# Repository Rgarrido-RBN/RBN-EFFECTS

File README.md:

# RBN-EFFECTS

## EN/

These are some of the projects I built and I make my own layout. Feel free to extend my work and experiment or modify whith them. 
Some of them are not verified, so before building them please check the schematic and the layout of the project.

**Non for comercial use.**

## ES/

Estos son algunos de los proyectos que he ido desarrollando por mi cuenta. Siéntete libre de fabricarlos y modificarlos. 
Algunos de los diseños no están verificados, si vas a construir alguno directamente asegurate de que el esquematico y las pistas estan corregidas.

**No para un uso comercial.**

Any suggestion or doubt contact me on rgarrido.rbn@gmail.com

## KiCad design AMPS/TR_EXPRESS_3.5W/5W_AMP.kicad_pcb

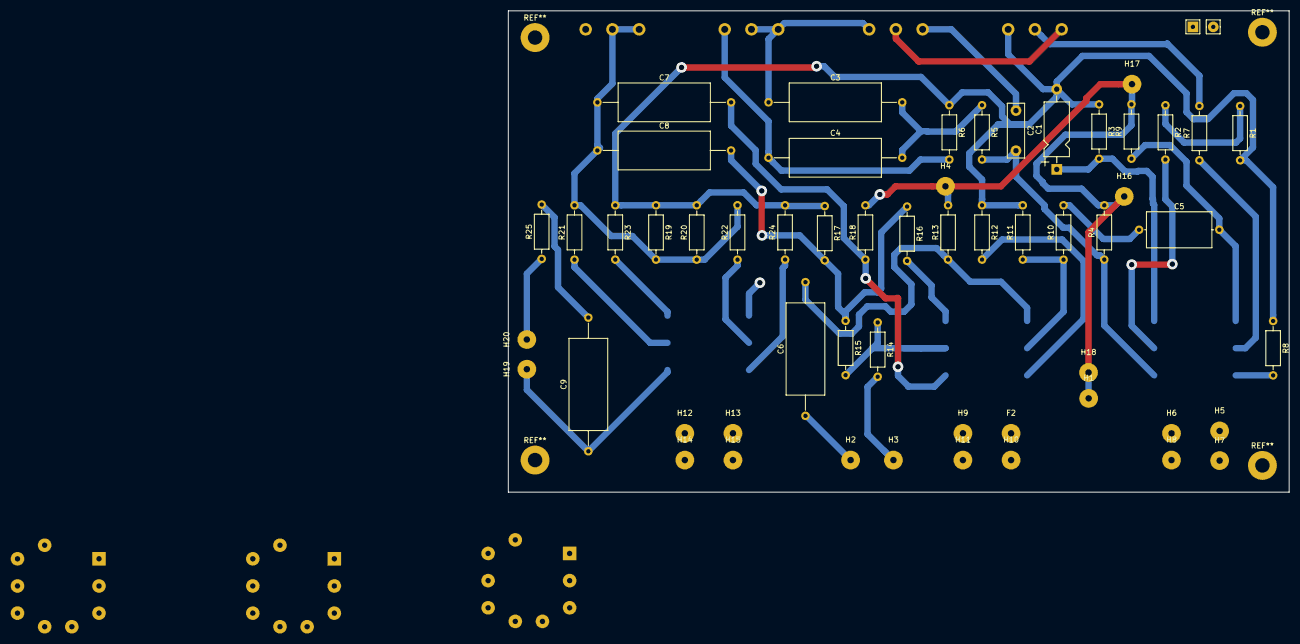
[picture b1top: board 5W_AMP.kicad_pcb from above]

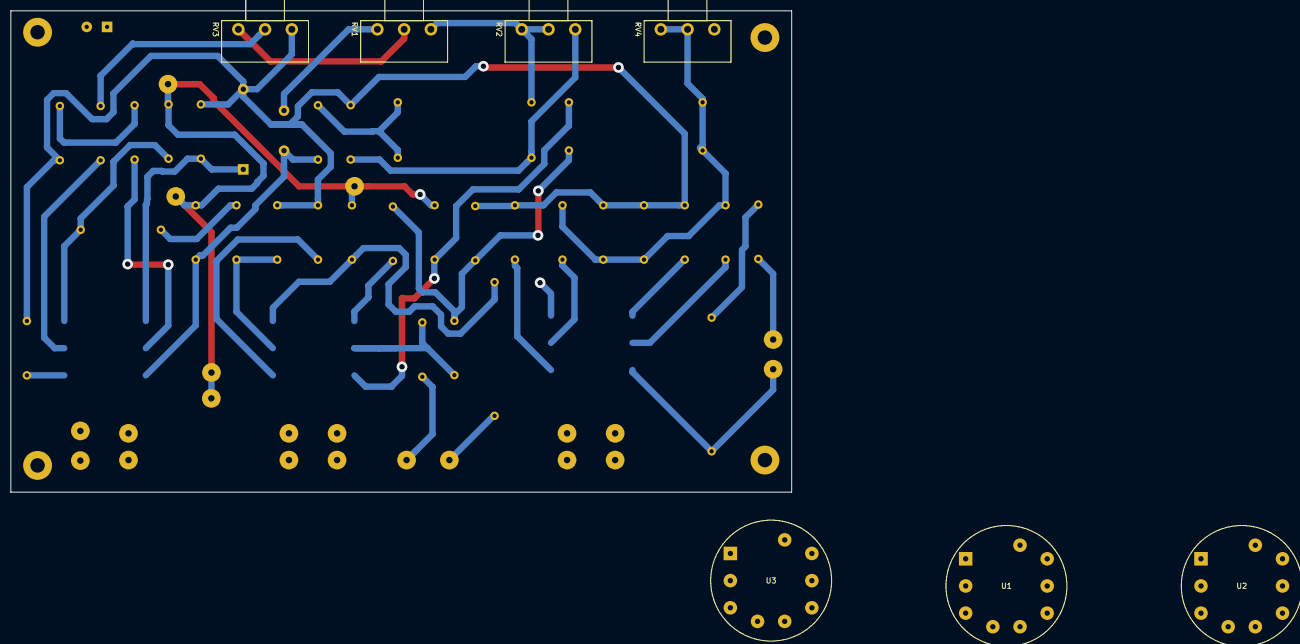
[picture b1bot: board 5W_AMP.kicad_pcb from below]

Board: 2 copper layers, 146.0 x 90.0 mm, 63 parts (7 on the bottom side), 39 nets.

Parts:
C1: 1µ; CP_Axial_L10.0mm_D4.5mm_P15.00mm_Horizontal
C2: 500p; C_Rect_L10.0mm_W3.0mm_P7.50mm_FKS3_FKP3
C3, C4, C6, C7, C8, C9: 22n; C_Axial_L17.0mm_D7.0mm_P25.00mm_Horizontal
C5: 4n7; C_Axial_L12.0mm_D6.5mm_P15.00mm_Horizontal
F2: F2; SolderWirePad_1x01_Drill1.2mm
H1, H4, H16, H17, H18: B1+; SolderWirePad_1x01_Drill1.2mm
H2: SEND; SolderWirePad_1x01_Drill1.2mm
H3: RETURN; SolderWirePad_1x01_Drill1.2mm
H5, H6, H9, H12, H13, H19, H20: F2; SolderWirePad_1x01_Drill1.2mm
H7, H8, H10, H11, H14, H15: F1; SolderWirePad_1x01_Drill1.2mm
J1: AudioJack2; Audio_Jack_Mono
R1, R14: 1M; R_Axial_DIN0207_L6.3mm_D2.5mm_P10.16mm_Horizontal
R2: 68k; R_Axial_DIN0207_L6.3mm_D2.5mm_P10.16mm_Horizontal
R3, R12, R16: 1k5; R_Axial_DIN0207_L6.3mm_D2.5mm_P10.16mm_Horizontal
R4, R9, R13: 100k; R_Axial_DIN0207_L6.3mm_D2.5mm_P10.16mm_Horizontal
R5: 150k; R_Axial_DIN0207_L6.3mm_D2.5mm_P10.16mm_Horizontal
R6: 15k; R_Axial_DIN0207_L6.3mm_D2.5mm_P10.16mm_Horizontal
R7: 820R; R_Axial_DIN0207_L6.3mm_D2.5mm_P10.16mm_Horizontal
R8: 2k7; R_Axial_DIN0207_L6.3mm_D2.5mm_P10.16mm_Horizontal
R10, R11: 470k; R_Axial_DIN0207_L6.3mm_D2.5mm_P10.16mm_Horizontal
R15, R19, R20: 220k; R_Axial_DIN0207_L6.3mm_D2.5mm_P10.16mm_Horizontal
R17, R18: 47k; R_Axial_DIN0207_L6.3mm_D2.5mm_P10.16mm_Horizontal
R21, R22: 22k; R_Axial_DIN0207_L6.3mm_D2.5mm_P10.16mm_Horizontal
R23, R24: 560R; R_Axial_DIN0207_L6.3mm_D2.5mm_P10.16mm_Horizontal
R25: 10k; R_Axial_DIN0207_L6.3mm_D2.5mm_P10.16mm_Horizontal
RV1, RV4: A250k; Potentiometer_Piher_T-16H_Single_Horizontal
RV2, RV3: A1M; Potentiometer_Piher_T-16H_Single_Horizontal
U1, U2: ECC83; Valve_Noval_P
U3: ECC99; Valve_Noval_P

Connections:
B1: H1.1, H4.1, H16.1, H17.1, H18.1, R4.2, R9.2, R13.2, R18.2
GND: C1.2, R1.2, R3.1, R6.1, R8.1, R11.2, R12.1, R17.1, R19.1, R20.2, R23.1, R24.2, RV3.1
unnamed: C1.1, R3.2, U1.8
unnamed: C2.1, RV1.3
unnamed: C2.2, R4.1, R5.2, U1.6
unnamed: C3.1, RV1.1, RV2.2, RV2.3
unnamed: C3.2, C4.2, R5.1
unnamed: C4.1, R6.2, RV2.1
unnamed: C5.1, R10.2
unnamed: C5.2, R9.1, U1.1
unnamed: C6.1, H2.1
unnamed: C6.2, R13.1, U2.1
unnamed: C7.1, C8.1, R19.2, R20.1, R21.2, R22.2, RV4.2, RV4.3
unnamed: C7.2, R18.1, U2.6
unnamed: C8.2, R15.1, R16.1, R17.2
unnamed: C9.1, H19.1, U3.6
unnamed: C9.2, R25.2
unnamed: F2.1, H9.1, U2.9
unnamed: H3.1, R14.2
unnamed: H5.1, H6.1, U1.9
unnamed: H7.1, H8.1, U1.4, U1.5
unnamed: H10.1, H11.1, U2.4, U2.5
unnamed: H12.1, H13.1, U3.9
unnamed: H14.1, H15.1, U3.4, U3.5
unnamed: H20.1, R25.1, U3.1
unnamed: R1.1, R2.1
unnamed: R2.2, U1.7
unnamed: R7.1, U1.2
unnamed: R7.2, RV3.2
unnamed: R8.2, U1.3
unnamed: R10.1, R11.1, U2.2
unnamed: R12.2, U2.3
unnamed: R14.1, R15.2, U2.7
unnamed: R16.2, U2.8
unnamed: R21.1, U3.7
unnamed: R22.1, U3.2
unnamed: R23.2, U3.8
unnamed: R24.1, U3.3
unnamed: RV1.2, RV3.3

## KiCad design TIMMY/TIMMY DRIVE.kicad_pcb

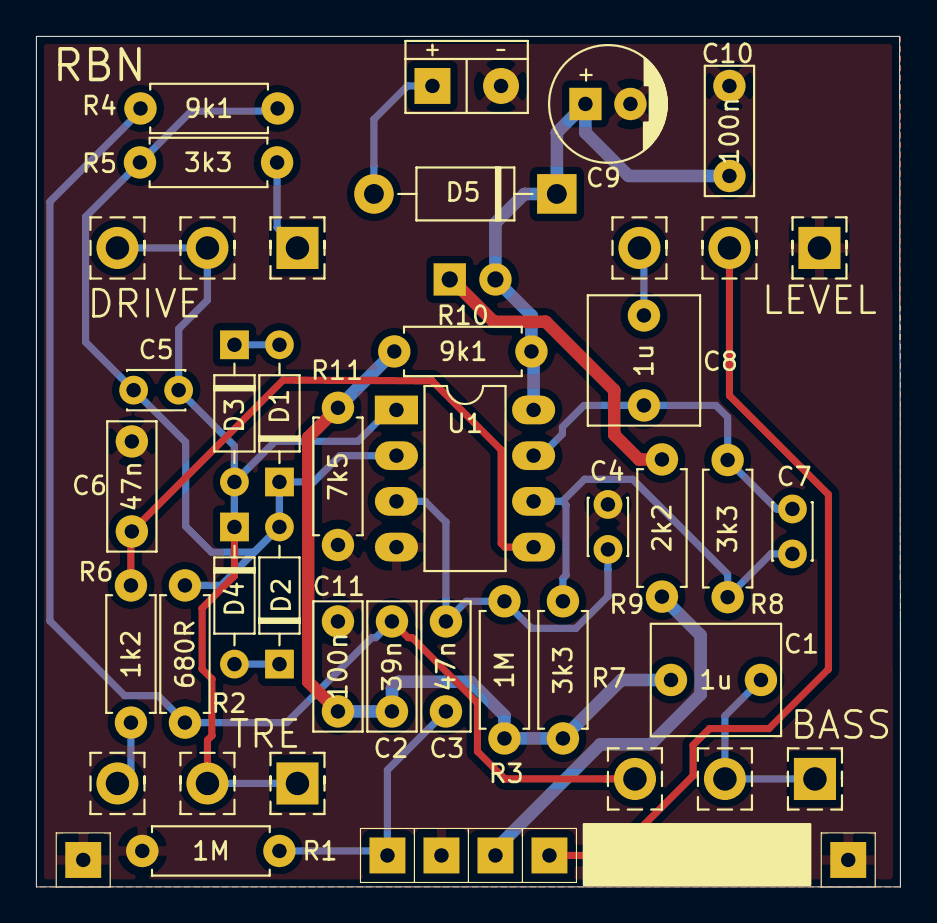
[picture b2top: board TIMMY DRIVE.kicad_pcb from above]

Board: 2 copper layers, 48.0 x 47.2 mm, 40 parts (1 on the bottom side), 21 nets.

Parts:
BT1: Battery_Cell; PWR_CON
C1, C8: 1u; Cap_poly_big
C2: 39n; Cap_poly_little
C3, C6: 47n; Cap_poly_little
C4: 22p; C_Disc_D3.0mm_W2.0mm_P2.50mm
C5: 47p; C_Disc_D3.0mm_W2.0mm_P2.50mm
C7: 150p; C_Disc_D3.0mm_W2.0mm_P2.50mm
C9: 47u; CP_Radial_D6.3mm_P2.50mm
C10, C11: 100n; Cap_poly_little
D1, D2, D3, D4: Si; D_DO-35_SOD27_P7.62mm_Horizontal
D5: D; D_DO-41_SOD81_P10.16mm_Horizontal
D6: LED; LED_D5.0mm
H3, H4, H5: GND; SolderWirePad_1x01_Drill0.8mm
H12: SW; SolderWirePad_1x01_Drill0.8mm
H14: FX.IN; SolderWirePad_1x01_Drill0.8mm
H16: FX.OUT; SolderWirePad_1x01_Drill0.8mm
R1, R3: 1M; R_0.25W_HZ
R2: 680R; R_0.25W_HZ
R4, R10: 9k1; R_0.25W_HZ
R5, R7, R8: 3k3; R_0.25W_HZ
R6: 1k2; R_0.25W_HZ
R9: 2k2; R_0.25W_HZ
R11: 7k5; R_0.25W_HZ
RV1: B50k; Pot_16_Alpha
RV3: B500k; Pot_16_Alpha
RV4, RV5: B10k; Pot_16_Alpha
U1: TL072; DIP-8_W7.62mm_LongPads

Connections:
FX.IN: C3.1, H14.1, R1.1
FX.OUT: H16.1, RV5.2
GND: BT1.2, C4.1, C6.1, C9.2, C10.1, C11.1, H3.1, H4.1, H5.1, R1.2, R11.1, RV5.1, U1.4
unnamed: BT1.1, D5.2
unnamed: C1.2, RV1.1, RV1.2
unnamed: C2.2, R2.1, R4.1, RV1.3
unnamed: C3.2, C4.2, R3.1, U1.3
unnamed: C5.1, D1.1, D2.2, R2.2, R4.2, R5.1, U1.2
unnamed: C5.2, D3.2, D4.1, RV3.2, RV3.3, RV4.1, RV4.2, U1.1
unnamed: C6.2, R6.2, U1.5
unnamed: C7.1, C8.2, R8.2, U1.7
unnamed: C7.2, R7.2, R8.1, U1.6
unnamed: C8.1, RV5.3
unnamed: C9.1, C10.2, D5.1, D6.2, R10.1, U1.8
unnamed: D1.2, D3.1
unnamed: D2.1, D4.2
unnamed: D6.1, R9.1
unnamed: R5.2, RV3.1
unnamed: R6.1, RV4.3
SW: H12.1, R9.2
Vref: C1.1, C2.1, C11.2, R3.2, R7.1, R10.2, R11.2

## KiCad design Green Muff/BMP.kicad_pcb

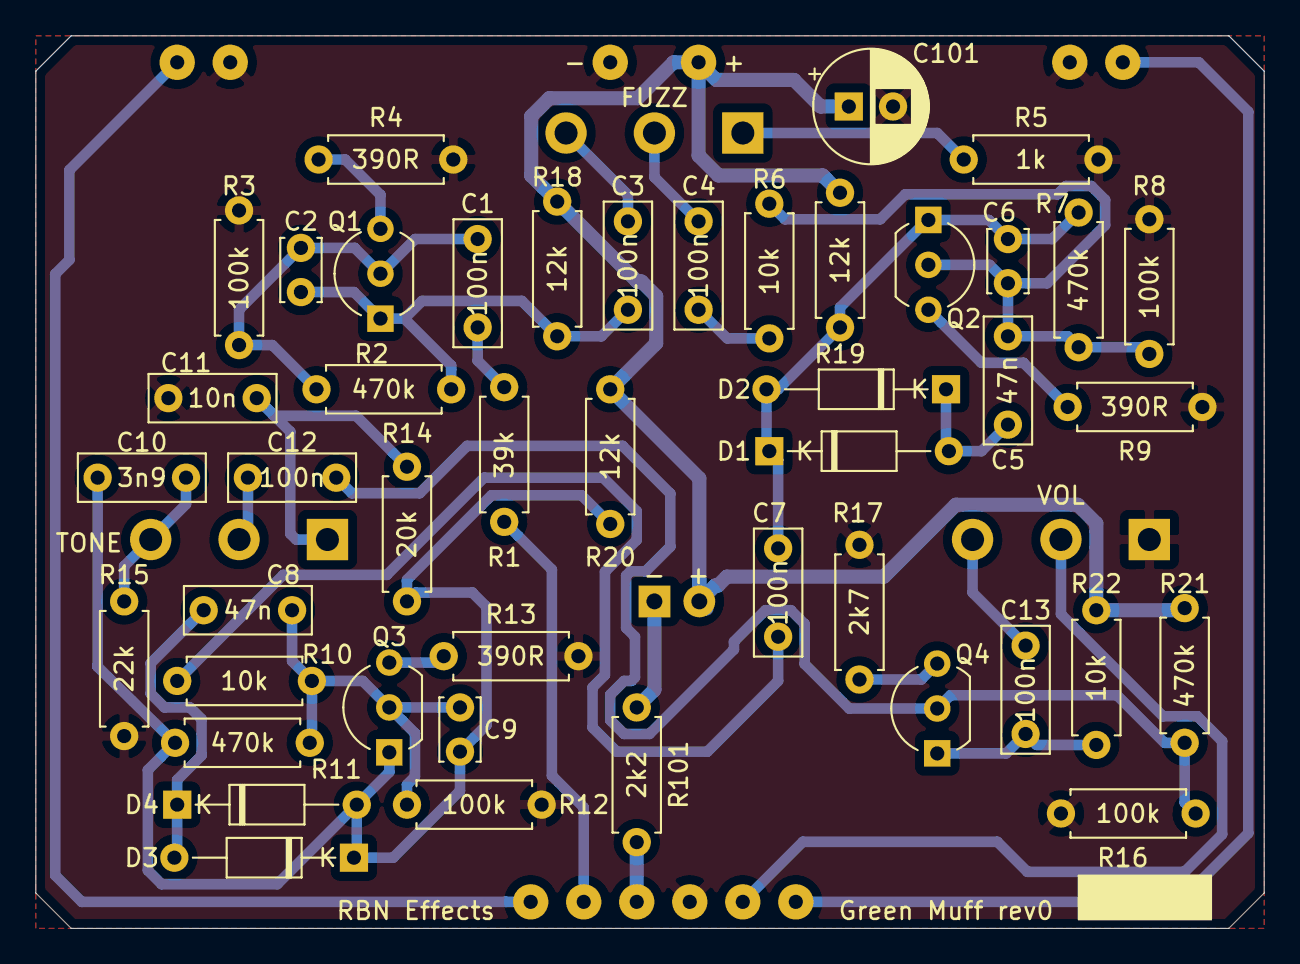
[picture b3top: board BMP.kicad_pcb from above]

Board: 2 copper layers, 69.5 x 50.5 mm, 61 parts (1 on the bottom side), 32 nets.

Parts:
C1, C3, C4, C7, C12, C13: 100n; Cap_POLY_SMALL
C2, C6, C9: 470p; C_Disc_D3.4mm_W2.1mm_P2.50mm
C5, C8: 47n; Cap_POLY_SMALL
C10: 3n9; Cap_POLY_SMALL
C11: 10n; Cap_POLY_SMALL
C101: 22u; CP_Radial_D6.3mm_P2.50mm
D1, D2, D3, D4: 1N914; D_DO-35_SOD27_P10.16mm_Horizontal
D5: LED; LED_D5.0mm
H2, H3: IN; SolderWirePad_1x01_Drill0.8mm
H4, H9: OUT; SolderWirePad_1x01_Drill0.8mm
H5: 9V; SolderWirePad_1x01_Drill0.8mm
H6, H7, H8, H10: GND; SolderWirePad_1x01_Drill0.8mm
H11: OUT FX; SolderWirePad_1x01_Drill0.8mm
H14: SW; SolderWirePad_1x01_Drill0.8mm
H15: IN FX; SolderWirePad_1x01_Drill0.8mm
Q1, Q2, Q3, Q4: BC549C; TO-92_Inline_Wide
R1: 39k; R_0.25W_HZ
R2, R7, R11, R21: 470k; R_0.25W_HZ
R3, R8, R12, R16: 100k; R_0.25W_HZ
R4, R9, R13: 390R; R_0.25W_HZ
R5: 1k; R_0.25W_HZ
R6, R10, R22: 10k; R_0.25W_HZ
R14: 20k; R_0.25W_HZ
R15: 22k; R_0.25W_HZ
R17: 2k7; R_0.25W_HZ
R18, R19, R20: 12k; R_0.25W_HZ
R101: 2k2; R_0.25W_HZ
RV1, RV2, RV3: B100k; Potentiometer_Piher_T-16L_Single_Vertical_Hole_MOD

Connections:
GND: C11.1, C101.2, H6.1, H7.1, H8.1, H10.1, R3.2, R4.2, R5.2, R8.2, R9.2, R12.2, R13.2, R15.2, R16.1, R17.1, RV3.1
IN: H2.1, H3.1
IN_FX: H15.1, R1.1
unnamed: C1.1, R1.2
unnamed: C1.2, C2.1, Q1.2, R2.1, R3.1
unnamed: C2.2, C3.1, Q1.1, R2.2, R18.2
unnamed: C3.2, RV1.3
unnamed: C4.1, RV1.2
unnamed: C4.2, R6.1
unnamed: C5.1, C6.1, Q2.2, R6.2, R7.1, R8.1
unnamed: C5.2, D1.2, D2.1
unnamed: C6.2, C7.1, D1.1, D2.2, Q2.1, R7.2, R19.2
unnamed: C7.2, R10.1
unnamed: C8.1, C9.1, Q3.2, R10.2, R11.1, R12.1
unnamed: C8.2, D3.2, D4.1
unnamed: C9.2, C10.1, D3.1, D4.2, Q3.1, R11.2, R14.1, R20.2
unnamed: C10.2, R15.1, RV2.3
unnamed: C11.2, R14.2, RV2.1
unnamed: C12.1, Q4.2, R16.2, R21.1
unnamed: C12.2, RV2.2
unnamed: C13.1, RV3.3
unnamed: C13.2, Q4.1, R22.1
unnamed: D5.1, R101.1
unnamed: Q1.3, R4.1
unnamed: Q2.3, R9.1
unnamed: Q3.3, R13.1
unnamed: Q4.3, R17.2
unnamed: R5.1, RV1.1
OUT: H4.1, H9.1
OUT_FX: H11.1, RV3.2
SW: H14.1, R101.2
V+: C101.1, D5.2, H5.1, R18.1, R19.1, R20.1, R21.2, R22.2

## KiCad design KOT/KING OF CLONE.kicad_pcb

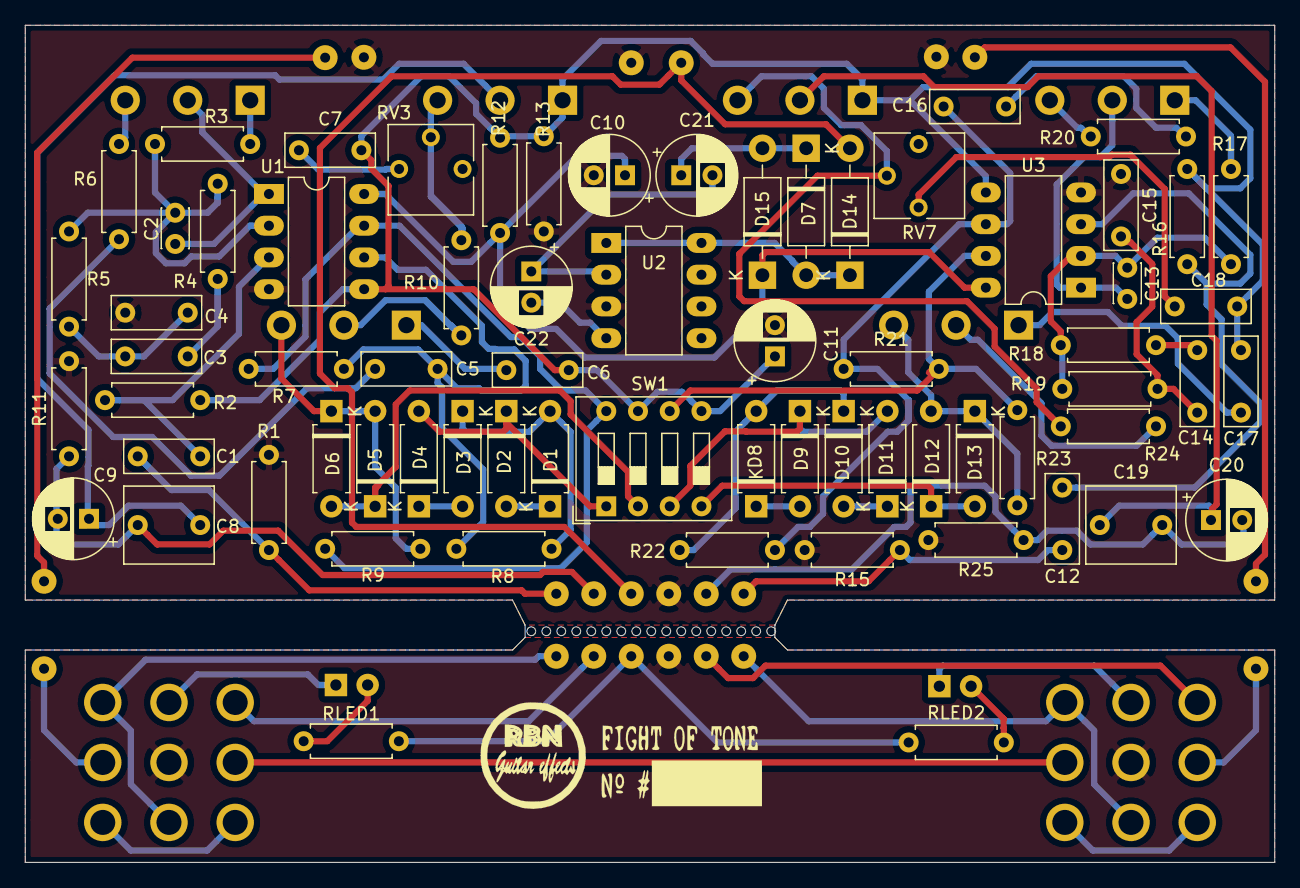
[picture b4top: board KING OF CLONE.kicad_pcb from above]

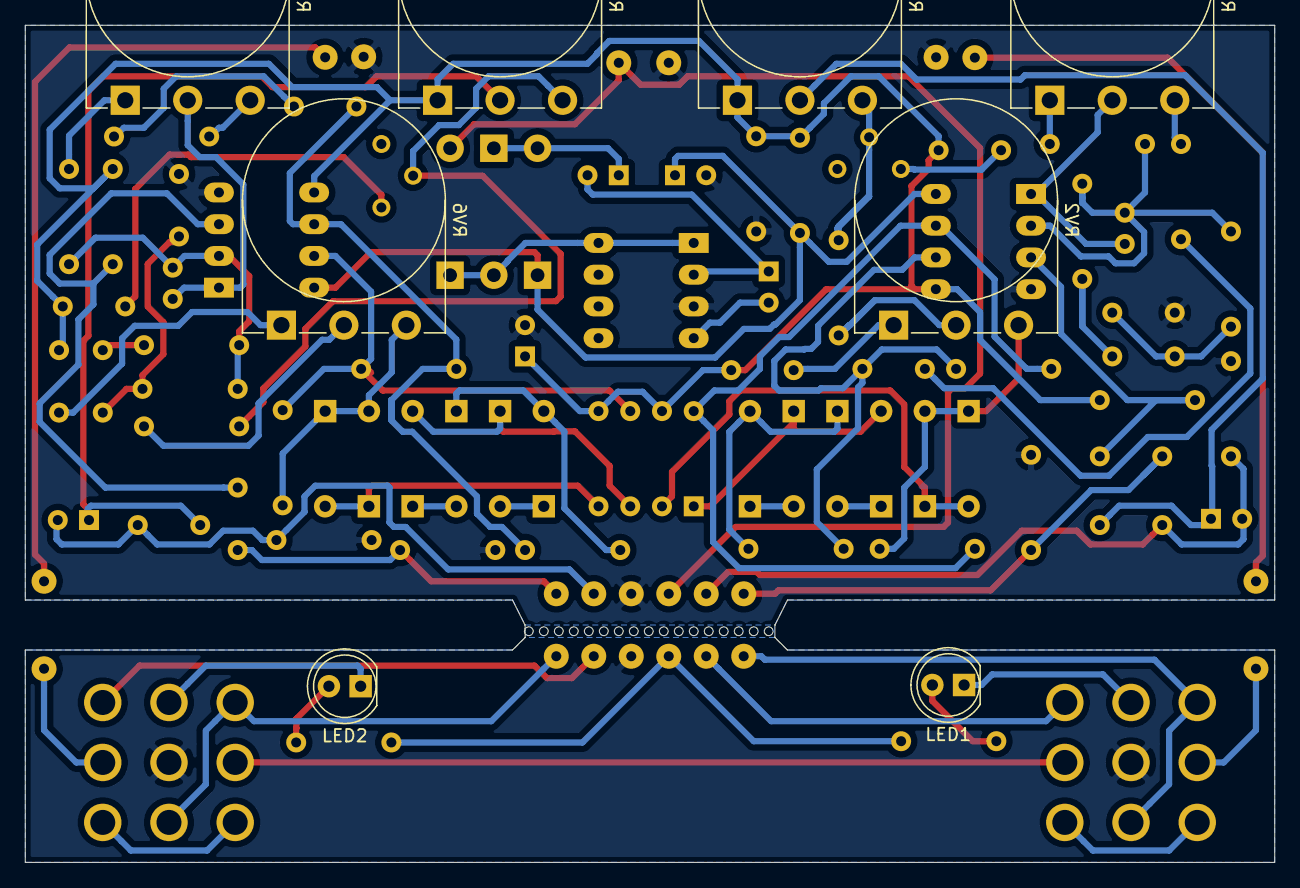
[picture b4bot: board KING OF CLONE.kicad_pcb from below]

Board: 2 copper layers, 100.0 x 67.0 mm, 101 parts (2 on the bottom side), 63 nets.

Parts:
C1, C3, C4, C6, C7, C12, C14, C15, C17, C18: 10n; C_Rect_L7.0mm_W2.5mm_P5.00mm
C2, C13: 100p; C_Disc_D3.0mm_W2.0mm_P2.50mm
C5, C16: 100n; C_Rect_L7.0mm_W2.5mm_P5.00mm
C8, C19: 1u; C_Rect_L7.0mm_W6.0mm_P5.00mm
C9, C20: 1u; CP_Radial_D6.3mm_P2.50mm
C10, C21, C22: 10u; CP_Radial_D6.3mm_P2.50mm
C11: 100u; CP_Radial_D6.3mm_P2.50mm
D1, D2, D3, D4, D8, D9, D10, D11: MA856; D_A-405_P7.62mm_Horizontal
D5, D6, D12, D13: 1S1588; D_A-405_P7.62mm_Horizontal
D7, D14, D15: 5817; D_DO-41_SOD81_P10.16mm_Horizontal
H1, H7, H9, H13, H15, H101, H103: IN; SolderWirePad_1x01_Drill0.8mm
H2, H8, H10, H14, H16, H102, H104: OUT; SolderWirePad_1x01_Drill0.8mm
H3, H11, H17: 9V; SolderWirePad_1x01_Drill0.8mm
H4, H5, H6, H12, H18: GND; SolderWirePad_1x01_Drill0.8mm
LED1, LED2: LED; LED_D5.0mm
R1, R2, R11, R15, R16, R25: 1M; R_Axial_DIN0207_L6.3mm_D2.5mm_P7.62mm_Horizontal
R3, R6, R17, R20: 10k; R_Axial_DIN0207_L6.3mm_D2.5mm_P7.62mm_Horizontal
R4, R18: 33k; R_Axial_DIN0207_L6.3mm_D2.5mm_P7.62mm_Horizontal
R5, R19: 27k; R_Axial_DIN0207_L6.3mm_D2.5mm_P7.62mm_Horizontal
R7, R21: 220k; R_Axial_DIN0207_L6.3mm_D2.5mm_P7.62mm_Horizontal
R8, R10, R22, R24: 6k8; R_Axial_DIN0207_L6.3mm_D2.5mm_P7.62mm_Horizontal
R9, R23: 1k; R_Axial_DIN0207_L6.3mm_D2.5mm_P7.62mm_Horizontal
R12, R13: 47k; R_Axial_DIN0207_L6.3mm_D2.5mm_P7.62mm_Horizontal
RLED1, RLED2: 2k2; R_Axial_DIN0207_L6.3mm_D2.5mm_P7.62mm_Horizontal
RV1, RV5: B100K; Potentiometer_Piher_T-16L_Single_Vertical_Hole_MOD
RV2, RV6: B25K; Potentiometer_Piher_T-16L_Single_Vertical_Hole_MOD
RV3, RV7: B50K; Potentiometer_Vishay_T73YP_Vertical
RV4, RV8: A100K; Potentiometer_Piher_T-16L_Single_Vertical_Hole_MOD
SW1: SW_DIP_4_2cases; SW_DIP_SPSTx04_Slide_9.78x12.34mm_W7.62mm_P2.54mm
SW2, SW3: 3pdt; 3PDT
U1, U3: RC4580; DIP-8_W7.62mm_LongPads
U2: MAX1044; DIP-8_W7.62mm_LongPads

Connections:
+9V: D7.2, H3.1, H11.1, H17.1, RLED1.1, RLED2.1
/POWER_SUPPLY/18V: C21.1, D14.1, D15.2
/POWER_SUPPLY/VCC: C10.1, D15.1, R12.1, U1.8, U3.8
COMMON: SW2.6, SW3.4
GND: C4.2, C10.2, C11.2, C15.2, H4.1, H5.1, H6.1, H12.1, H18.1, R1.2, R11.2, R13.2, R15.2, R25.2, SW2.5, SW3.5, U1.4, U2.3, U3.4
IN1: C1.2, H7.1, H13.1, R1.1, SW2.2, SW2.7
IN2: C12.2, H9.1, H15.1, R15.1, SW3.2, SW3.7
JACK_IN: H1.1, H101.1, H103.1, SW2.4
JACK_OUT: H2.1, H102.1, H104.1, SW3.6
unnamed: C1.1, R2.2, U1.3
unnamed: C2.1, RV1.2, U1.1
unnamed: C2.2, R3.2, R4.2, R5.1, U1.2
unnamed: C3.1, R4.1
unnamed: C3.2, C4.1, R5.2
unnamed: C5.1, R7.1, R8.1, U1.6
unnamed: C5.2, R6.2
unnamed: C6.1, RV2.1
unnamed: C7.1, RV3.3
unnamed: C8.1, C9.1, RV4.2
unnamed: C12.1, R16.2, U3.3
unnamed: C13.1, RV5.2, U3.1
unnamed: C13.2, R17.2, R18.2, R19.1, U3.2
unnamed: C14.1, R18.1
unnamed: C14.2, C15.1, R19.2
unnamed: C16.1, R21.1, R22.1, U3.6
unnamed: C16.2, R20.2
unnamed: C17.1, RV6.1
unnamed: C18.1, RV7.3
unnamed: C19.1, C20.1, RV8.2
unnamed: C21.2, C22.1, U2.2
unnamed: C22.2, U2.4
unnamed: D1.1, D2.2
unnamed: D1.2, D3.1, R8.2
unnamed: D2.1, D4.2, SW1.1
unnamed: D3.2, D4.1
unnamed: D5.1, D6.2, SW1.2
unnamed: D5.2, D6.1, R9.2, RV2.3
unnamed: D8.1, D9.2
unnamed: D8.2, D10.1, R22.2
unnamed: D10.2, D11.1
unnamed: D9.1, D11.2, SW1.3
unnamed: D12.1, D13.2, SW1.4
unnamed: D12.2, D13.1, R23.2, RV6.3
unnamed: D7.1, D14.2, U2.1, U2.8
unnamed: LED1.2, RLED1.2
unnamed: LED2.2, RLED2.2
unnamed: R3.1, RV1.1
unnamed: R6.1, RV1.3
unnamed: R7.2, R9.1, SW1.8, U1.7
unnamed: R10.1, RV2.2
unnamed: R10.2, RV3.2, RV4.3
unnamed: R17.1, RV5.1
unnamed: R20.1, RV5.3
unnamed: R21.2, R23.1, SW1.6, U3.7
unnamed: R24.1, RV6.2
unnamed: R24.2, RV7.2, RV8.3
unnamed: SW2.1, SW2.3
unnamed: SW3.1, SW3.3
OUT1: C8.2, C9.2, H8.1, H14.1, R11.1, SW2.9
OUT2: C19.2, C20.2, H10.1, H16.1, R25.1, SW3.9
SW1: LED1.1, SW2.8
SW2: LED2.1, SW3.8
VREF: C6.2, C7.2, C11.1, C17.2, C18.2, R2.1, R12.2, R13.1, R16.1, RV4.1, RV8.1, SW1.5, SW1.7, U1.5, U3.5

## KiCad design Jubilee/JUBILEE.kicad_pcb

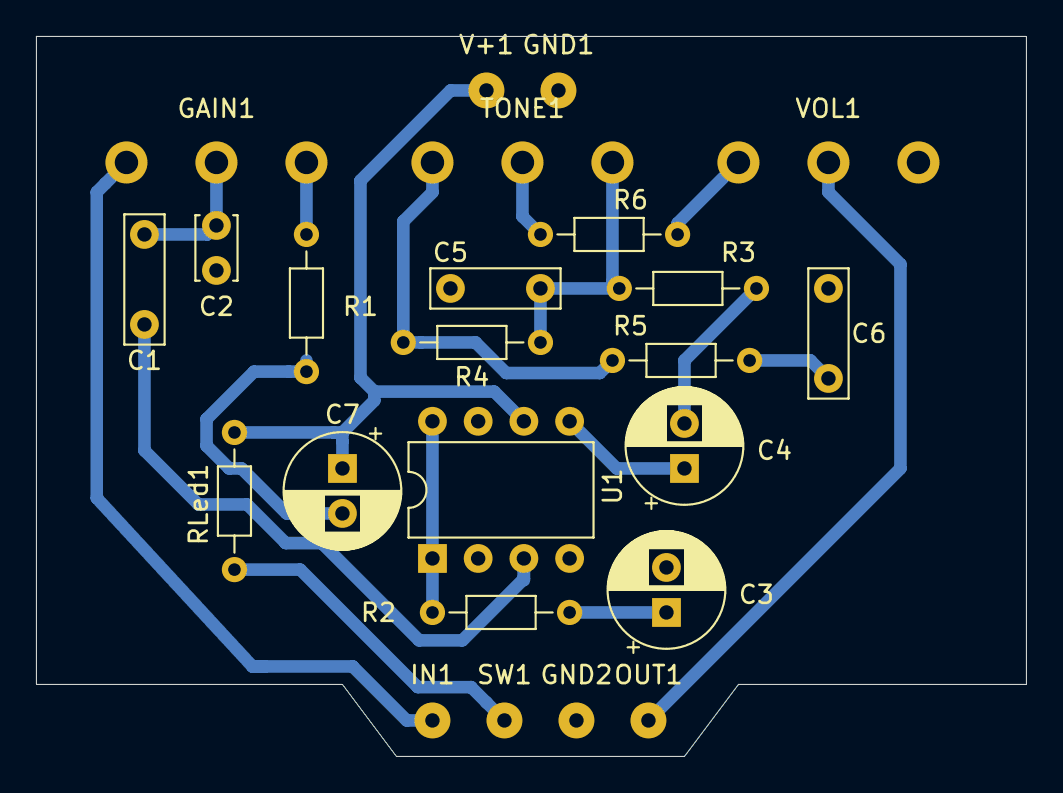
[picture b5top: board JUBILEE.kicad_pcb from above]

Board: 2 copper layers, 55.0 x 40.0 mm, 24 parts (0 on the bottom side), 17 nets.

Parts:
C1: 390p; C_Disc_D3.4mm_W2.1mm_P2.50mm
C2, C5: 22n; C_Rect_L7.0mm_W2.0mm_P5.00mm
C3, C4, C7: 47u; CP_Radial_D6.3mm_P2.50mm
C6: 100n; C_Rect_L7.0mm_W2.0mm_P5.00mm
GAIN1: A250k; Potentiometer_Piher_T-16L_Single_Vertical_Hole_MOD
GND1, GND2: MountingHole_Pad; SolderWirePad_1x01_Drill0.8mm
IN1: MountingHole_Pad; SolderWirePad_1x01_Drill0.8mm
OUT1: MountingHole_Pad; SolderWirePad_1x01_Drill0.8mm
R1, R3, R4: 4k7; R_Axial_DIN0204_L3.6mm_D1.6mm_P7.62mm_Horizontal
R2: 47R; R_Axial_DIN0204_L3.6mm_D1.6mm_P7.62mm_Horizontal
R5: 1k8; R_Axial_DIN0204_L3.6mm_D1.6mm_P7.62mm_Horizontal
R6: 330R; R_Axial_DIN0204_L3.6mm_D1.6mm_P7.62mm_Horizontal
RLed1: R; R_Axial_DIN0204_L3.6mm_D1.6mm_P7.62mm_Horizontal
SW1: MountingHole_Pad; SolderWirePad_1x01_Drill0.8mm
TONE1: B50k; Potentiometer_Piher_T-16L_Single_Vertical_Hole_MOD
U1: LM386; DIP-8_W7.62mm
V+1: MountingHole_Pad; SolderWirePad_1x01_Drill0.8mm
VOL1: A100k; Potentiometer_Piher_T-16L_Single_Vertical_Hole_MOD

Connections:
GND: C1.1, C3.2, C5.1, C6.1, C7.2, GND1.1, GND2.1, R1.2, U1.2, U1.4, VOL1.1
unnamed: C1.2, C2.1, GAIN1.2
unnamed: C2.2, U1.3
unnamed: C3.1, R2.2
unnamed: C4.1, U1.5
unnamed: C4.2, R3.1
unnamed: C5.2, R3.2, R4.1, TONE1.3
unnamed: C6.2, R5.2
unnamed: C7.1, RLed1.1, U1.6, V+1.1
unnamed: GAIN1.1, R1.1
unnamed: GAIN1.3, IN1.1
unnamed: OUT1.1, VOL1.2
unnamed: R2.1, U1.1, U1.8
unnamed: R4.2, R5.1, TONE1.1
unnamed: R6.1, TONE1.2
unnamed: R6.2, VOL1.3
unnamed: RLed1.2, SW1.1

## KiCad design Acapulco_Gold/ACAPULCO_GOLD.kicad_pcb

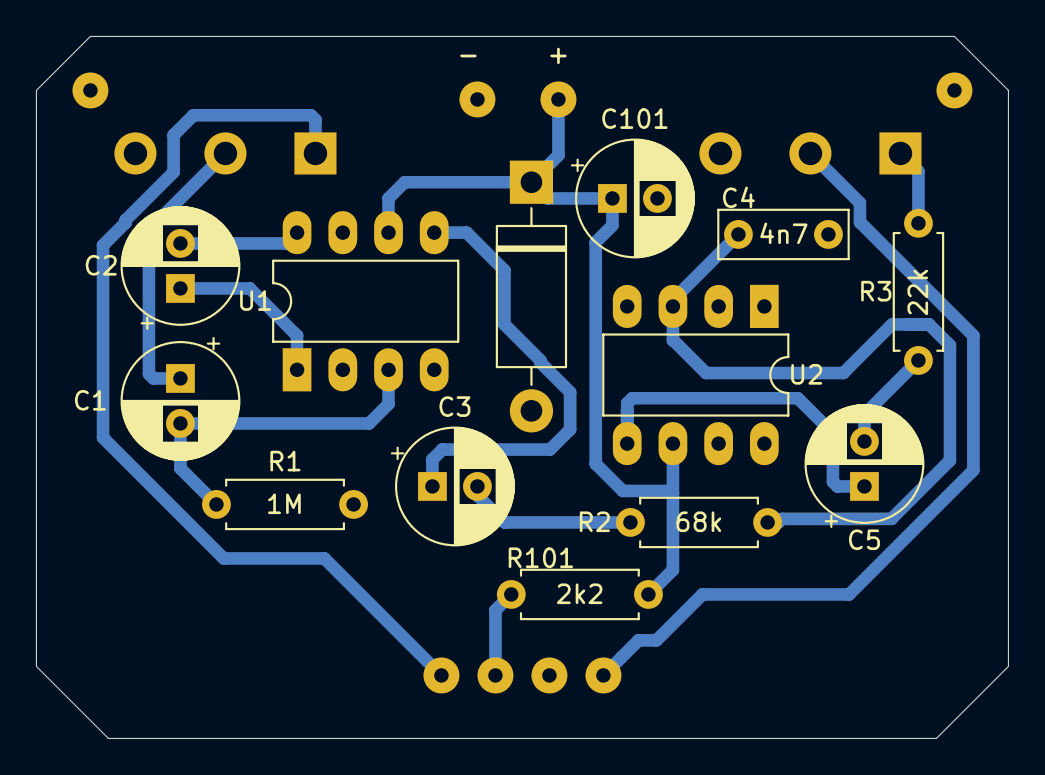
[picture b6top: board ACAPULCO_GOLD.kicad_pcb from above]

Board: 2 copper layers, 54.0 x 39.0 mm, 23 parts (0 on the bottom side), 15 nets.

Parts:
C1, C2: 10u; CP_Radial_D6.3mm_P2.50mm
C3, C5: 1u; CP_Radial_D6.3mm_P2.50mm
C4: 4n7; Cap_POLY_SMALL
C101: 47u; CP_Radial_D6.3mm_P2.50mm
D101: 1N4001; D_DO-15_P12.70mm_Horizontal
H5: PCB_OUT; SolderWirePad_1x01_Drill0.8mm
H6: PCB_IN; SolderWirePad_1x01_Drill0.8mm
H7, H8, H9, H10: GND; SolderWirePad_1x01_Drill0.8mm
H11: 9V; SolderWirePad_1x01_Drill0.8mm
H12: SW; SolderWirePad_1x01_Drill0.8mm
R1: 1M; R_0.25W_HZ
R2: 68k; R_0.25W_HZ
R3: 22k; R_0.25W_HZ
R101: 2k2; R_0.25W_HZ
RV1: A500k; Potentiometer_Piher_T-16L_Single_Vertical_Hole_MOD
RV2: A100k; Potentiometer_Piher_T-16L_Single_Vertical_Hole_MOD
U1, U2: LM386; DIP-8_W7.62mm_LongPads

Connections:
+9V: C101.1, D101.1, H11.1, R101.1, U1.6, U2.6
GND: C4.2, C101.2, D101.2, H7.1, H8.1, H9.1, H10.1, R1.2, RV1.3, RV2.3, U1.2, U1.4, U2.2, U2.4
unnamed: C1.1, RV1.2
unnamed: C1.2, R1.1, U1.3
unnamed: C2.1, U1.1
unnamed: C2.2, U1.8
unnamed: C3.1, U1.5
unnamed: C3.2, R2.1
unnamed: C4.1, R2.2, U2.3
unnamed: C5.1, U2.5
unnamed: C5.2, R3.1
unnamed: R3.2, RV2.1
PCB_IN: H6.1, RV1.1
PCB_OUT: H5.1, RV2.2
SW: H12.1, R101.2

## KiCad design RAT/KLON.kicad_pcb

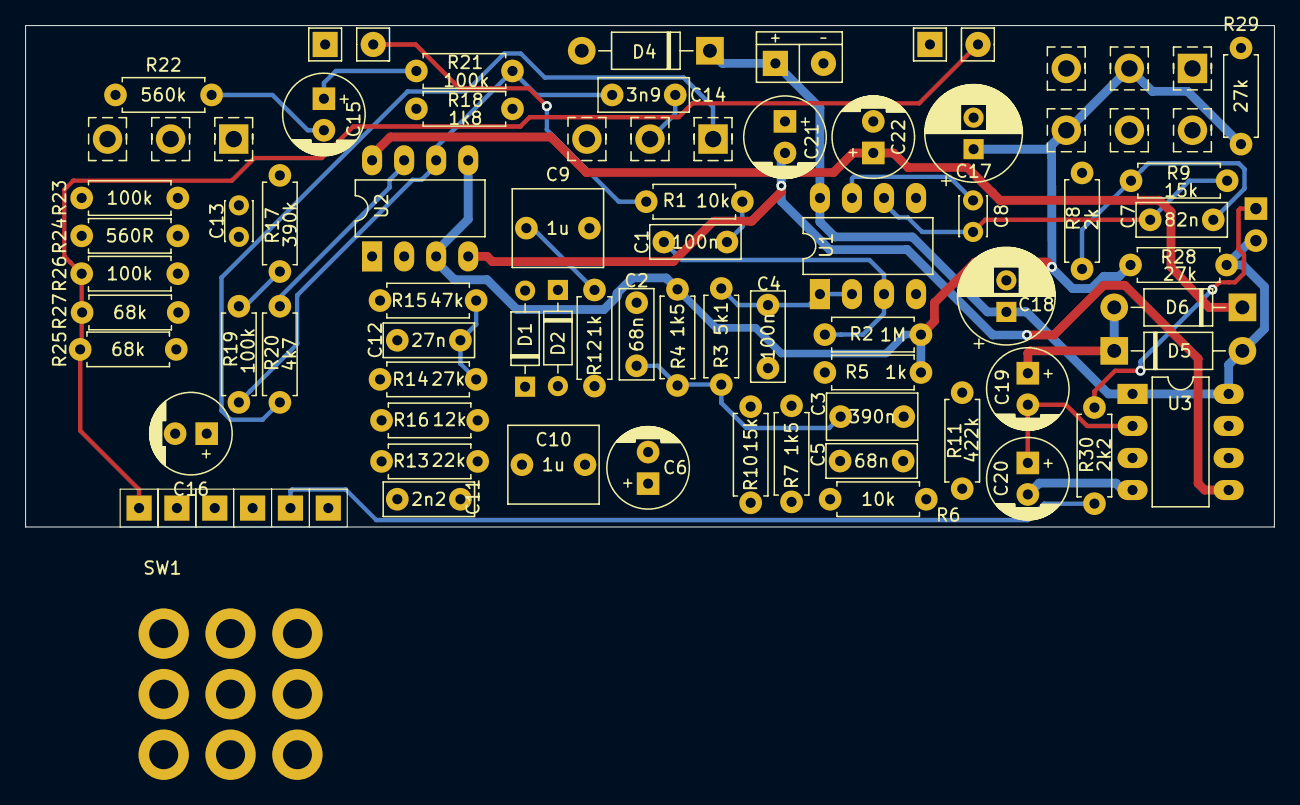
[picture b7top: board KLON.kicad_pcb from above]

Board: 2 copper layers, 99.0 x 39.8 mm, 75 parts (1 on the bottom side), 42 nets.

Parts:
1590B: 1590BB
BT1: Battery_Cell; PWR_CON
C1, C4: 100n; Cap_poly_little
C2, C5: 68n; Cap_poly_little
C3: 390n; Cap_poly_mid
C6, C19, C20, C21, C22: 1u; CP_Radial_D6.3mm_P2.50mm
C7: 82n; Cap_poly_little
C8: 390p; C_Disc_D3.0mm_W2.0mm_P2.50mm
C9, C10: 1u; Cap_poly_big
C11: 2n2; Cap_poly_little
C12: 27n; Cap_poly_little
C13: 820p; C_Disc_D3.0mm_W2.0mm_P2.50mm
C14: 3n9; Cap_poly_little
C15, C16: 4u7; CP_Radial_D6.3mm_P2.50mm
C17, C18: 47u; CP_Radial_D7.5mm_P2.50mm
D1: 1N34A; D_DO-35_SOD27_P7.62mm_Horizontal
D2: D; D_DO-35_SOD27_P7.62mm_Horizontal
D4: 1N4001; D_DO-41_SOD81_P10.16mm_Horizontal
D5, D6: 1N4007; D_DO-41_SOD81_P10.16mm_Horizontal
DLED1: LED; LED_D5.0mm
H4: OUT; SolderWirePad_1x01_Drill0.8mm
H5: GND; SolderWirePad_1x01_Drill0.8mm
H9: SW1.3; SolderWirePad_1x01_Drill0.8mm
H11: SW2.3; SolderWirePad_1x01_Drill0.8mm
H12: SW2.1; SolderWirePad_1x01_Drill0.8mm
H14: SW1.1; SolderWirePad_1x01_Drill0.8mm
J1: IN; Audio_Jack_Mono
J2: OUT; Audio_Jack_Mono
R1, R6: 10k; R_0.25W_HZ
R2: 1M; R_0.25W_HZ
R3: 5k1; R_0.25W_HZ
R4, R7: 1k5; R_0.25W_HZ
R5, R12: 1k; R_0.25W_HZ
R8: 2k; R_0.25W_HZ
R9, R10: 15k; R_0.25W_HZ
R11: 422k; R_0.25W_HZ
R13: 22k; R_0.25W_HZ
R14, R28, R29: 27k; R_0.25W_HZ
R15: 47k; R_0.25W_HZ
R16: 12k; R_0.25W_HZ
R17: 390k; R_0.25W_HZ
R18: 1k8; R_0.25W_HZ
R19, R21, R23, R26: 100k; R_0.25W_HZ
R20: 4k7; R_0.25W_HZ
R22: 560k; R_0.25W_HZ
R24: 560R; R_0.25W_HZ
R25, R27: 68k; R_0.25W_HZ
R30: 2k2; R_0.25W_HZ
RV1: B100k; Pot_16_Alpha_Doble
RV2: B10k; Pot_16_Alpha
RV3: A10k; Pot_16_Alpha
SW1: 3pdt; 3PDT
U1, U2: TL072; DIP-8_W7.62mm_LongPads
U3: LTC1044; DIP-8_W7.62mm_LongPads

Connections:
9V: BT1.1, C18.1, D4.1, D5.2, DLED1.2, R28.1, U1.8, U3.1, U3.8
-9V: C21.2, U2.4, U3.5
/18V: C22.1, D6.1, U2.8
/OUT: H4.1, J2.2, R25.1, R26.1, R27.1, SW1.4
GND: BT1.2, C6.2, C17.2, C18.2, C21.1, C22.2, D1.2, D2.1, D4.2, H5.1, J1.1, J2.1, R23.2, R26.2, R29.1, RV3.1, SW1.6, U1.4, U3.3
unnamed: C1.1, R1.2
unnamed: C1.2, R2.2, U1.3
unnamed: C2.1, C3.2, R3.1, R4.2, RV1.4
unnamed: C3.1, R5.2
unnamed: C4.1, C5.2, R6.2, R7.2
unnamed: C5.1, R6.1, RV1.1, U1.5
unnamed: C6.1, R7.1, R10.2
unnamed: C7.1, C8.2, R9.2, R11.1, U1.6
unnamed: C7.2, R8.2, R9.1
unnamed: C8.1, C9.2, R11.2, U1.7
unnamed: C9.1, R12.1
unnamed: C10.1, C11.1, R15.1
unnamed: C11.2, R13.2
unnamed: C12.1, C13.1, R10.1, R14.2, R15.2, R17.2, U2.2
unnamed: C12.2, R16.2
unnamed: C13.2, R17.1, R18.2, R19.2, U2.1
unnamed: C14.1, RV2.2
unnamed: C14.2, R19.1, R21.2, U2.6
unnamed: C15.1, R20.1, R21.1, U2.7
unnamed: C15.2, R22.2
unnamed: C2.2, C4.2, C16.1, R3.2, U1.1, U1.2
unnamed: C16.2, R23.1, R24.2
unnamed: C19.1, D5.1, D6.2
unnamed: C19.2, C20.1, U3.2
unnamed: C20.2, U3.4
unnamed: DLED1.1, R30.2
unnamed: J1.2, R1.1
unnamed: R8.1, RV1.3
unnamed: R13.1, R14.1, R16.1, RV1.5
unnamed: R18.1, RV2.3
unnamed: R20.2, RV2.1
unnamed: R22.1, RV3.3
SW1.1: H14.1, R24.1, R27.2, SW1.7
SW1.3: H9.1, R25.2, RV3.2, SW1.1
SW2.1: C10.2, D1.1, D2.2, H12.1, R12.2, SW1.9
SW2.3: H11.1, R30.1, SW1.3
VB: C17.1, R2.1, R4.1, R5.1, R28.2, R29.2, RV1.2, RV1.6, U2.3, U2.5

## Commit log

2021-01-15 Uploading my shared projects
2021-01-17 Adding my shared amps projects
